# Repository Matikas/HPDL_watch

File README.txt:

A watch with HPDL-2416 display and ATmega16 microcontroller.

Schematic and PCB is designed using Eagle. AVR code project created using Atmel Studio 6.

Don't forget to set right fuses when programming your AVR. Fuse bits for khazama AVR Programmer: \HPDL_watch\AVR code\Fuse bits.PNG

Project page: http://hackaday.io/project/1120-HPDL-watch

Contact me: snajper3@gmail.com

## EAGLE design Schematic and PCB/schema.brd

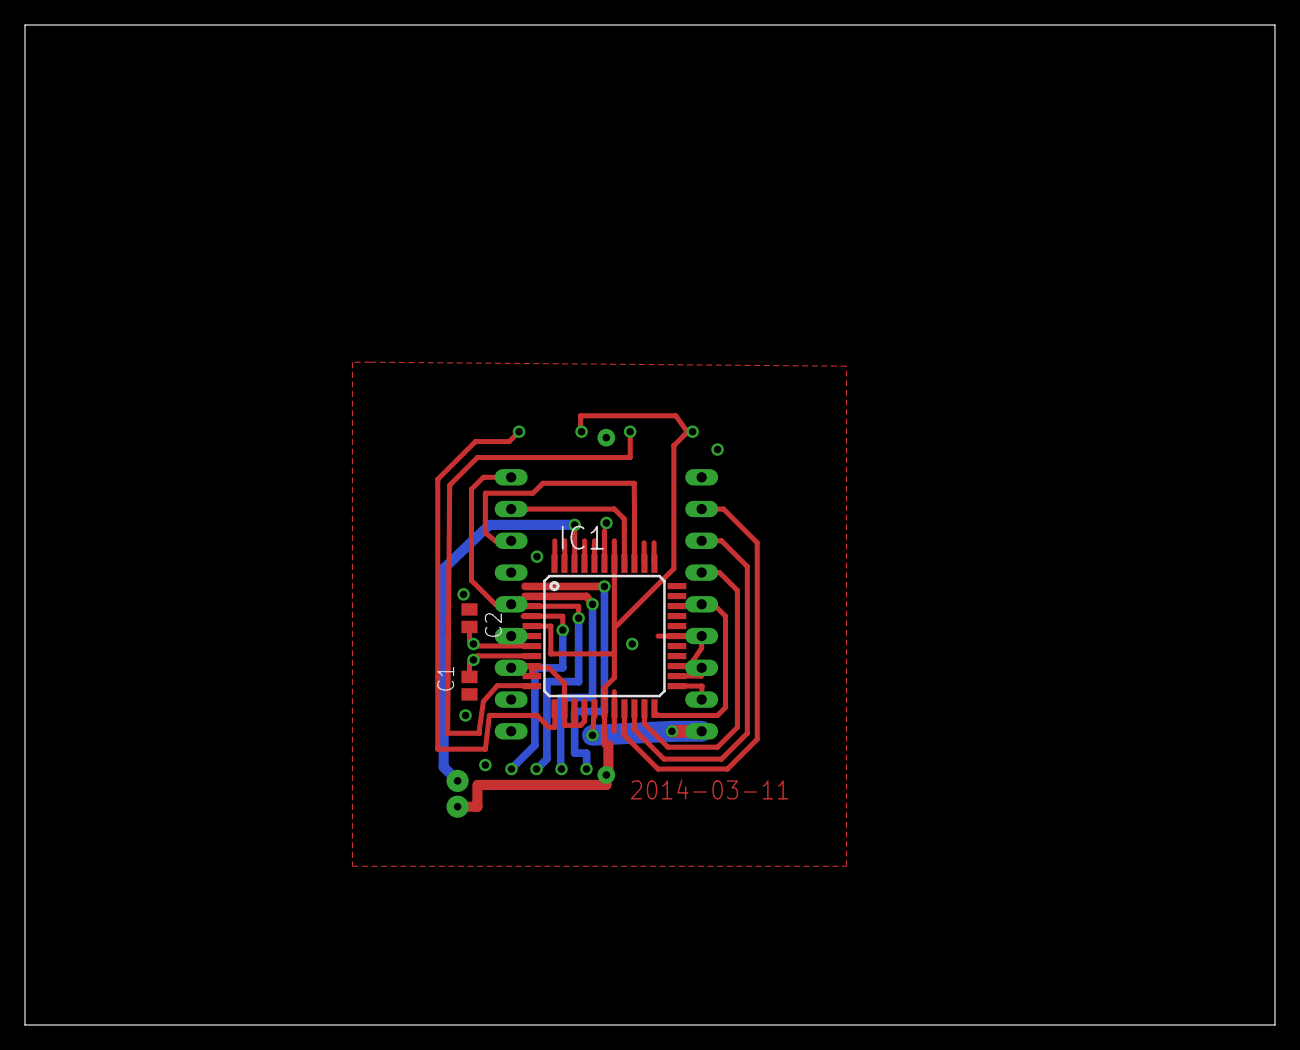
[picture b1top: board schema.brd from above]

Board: 2 copper layers, 100.0 x 80.0 mm, 4 parts (1 on the bottom side), 13 nets.

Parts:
C1, C2: C0504
DIS1: HDLX2416
IC1: MEGA16-A; TQFP44

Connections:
BL: DIS1.18, IC1.16
GND: C1.1, C2.1, DIS1.1, DIS1.2, DIS1.4, DIS1.6, DIS1.10, IC1.6, IC1.28
S$6: DIS1.7, IC1.36
S$7: DIS1.8, IC1.37
S$8: DIS1.11, IC1.19
S$9: DIS1.12, IC1.20
S$10: DIS1.13, IC1.21
S$11: DIS1.14, IC1.22
S$12: DIS1.15, IC1.25
S$13: DIS1.16, IC1.24
S$14: DIS1.17, IC1.23
S$20: IC1.9, IC1.10, IC1.13, IC1.14, IC1.15
VDD: DIS1.5, DIS1.9

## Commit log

2014-05-10 Readme
    Readme.txt added.
2014-05-10 All source added
2014-05-10 readme modified
2014-05-10 code fix
2014-05-10 code update
